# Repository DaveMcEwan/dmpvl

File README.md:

dmpvl - Dave McEwan's Personal Verilog Library
==============================================

Verilog/SystemVerilog projects.

  - doc - External documentation.
  - hdl - HDL (Hardware Description Language) code shared between projects.
  - misc - Miscellaneous items related to this repository.
  - mk - A collection of makefile fragments.
  - prj - A concrete realisation of code on a specific platform.
    May be a specific type of simulation, FPGA, or (wishfully!) ASIC.
    Each of these has some practical usecase.
  - prs - Presentation material like slidesets or papers.
  - tb - Testbenches for verifying modules by simulation.
    These don't really have any practical usecase other than verification.
  - verif - Components which may be shared between verification tasks.

FOSS tools are preferred.

  - iverilog - Traditional event based simulator.
  - verilator - Cycle accurate simulator.
  - yosys - Synthesis.
  - arachne-pnr - First-generation place-and-route for Lattice ice40 FPGAs.
  - nextpnr-ice40 - Second-generation place-and-route for Lattice ice40 FPGAs.
  - tinyprog - Bootloader interface utility for TinyFPGA series of boards.
  - icestorm - Collection of utilities for Lattice ice40 FPGAs.
  - gtkwave - Value Change Dump (VCD) waveform viewer.
    The config file here `.gtkwaverc` may be symlink/copied to `$HOME` or
    appropriate working directories.

Begin work with something like:
```
sudo make -f mk/tools.mk apt_prereqs
make -f tools.mk
export PATH=$PWD/tools/bin:$PATH
```

To track the size of this repo by number of lines of code:

    wc -l `find hdl/ prj/ tb/ verif/ -type f | grep -vP '(build|svg)'`

TODO: More writeup
TODO: Writeup each project.
TODO: Writeup each testbench.

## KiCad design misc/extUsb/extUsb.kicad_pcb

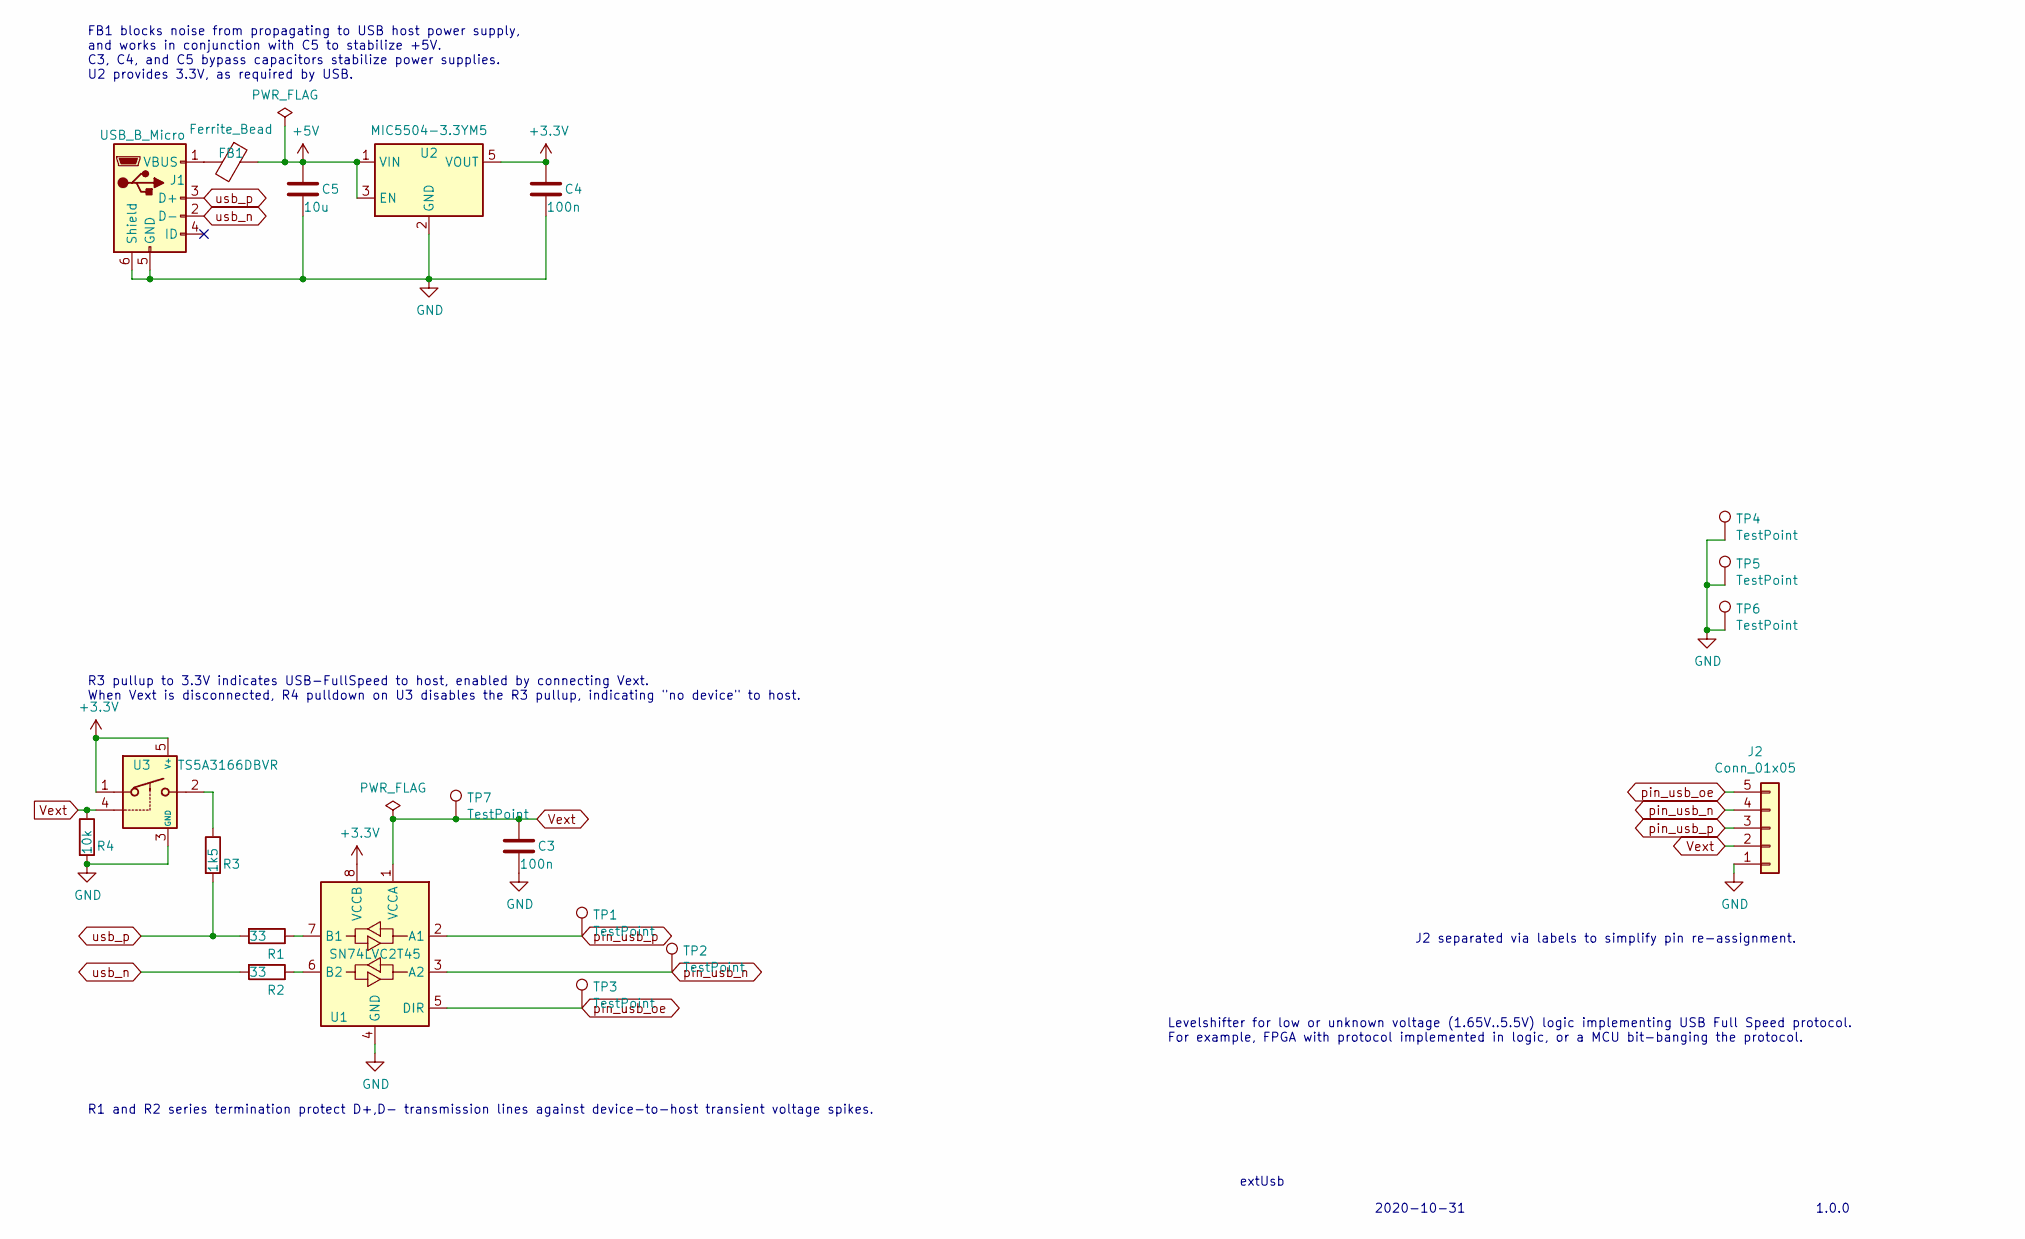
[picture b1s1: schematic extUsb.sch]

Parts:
C3, C4: 100n; C_0603_1608Metric_Pad1.08x0.95mm_HandSolder
C5: 10u; C_0603_1608Metric_Pad1.08x0.95mm_HandSolder
FB1: Ferrite_Bead; L_0603_1608Metric_Pad1.05x0.95mm_HandSolder
J1: USB_B_Micro; USB_Micro-B_Molex-105017-0001
J2: Conn_01x05; PinHeader_1x05_P2.54mm_Horizontal
R1, R2: 33; R_0603_1608Metric_Pad0.98x0.95mm_HandSolder
R3: 1k5; R_0603_1608Metric_Pad0.98x0.95mm_HandSolder
R4: 10k; R_0603_1608Metric_Pad0.98x0.95mm_HandSolder
TP1: TestPoint
TP2, TP3, TP4, TP5, TP6, TP7: TestPoint; TestPoint_Pad_D2.0mm
U1: SN74LVC2T45; SSOP-8_2.95x2.8mm_P0.65mm
U2: MIC5504-3.3YM5; SOT-23-5_HandSoldering
U3: TS5A3166DBVR; SOT-23-5_HandSoldering

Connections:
+3V3: C4.1, U1.8 (VCCB), U2.5 (VOUT), U3.1, U3.5 (V+)
+5V: C5.1, FB1.1, U2.1 (VIN), U2.3 (EN)
GND: C3.2, C4.2, C5.2, J1.5 (GND), J1.6 (Shield), J2.1, R4.2, TP4.1, TP5.1, TP6.1, U1.4 (GND), U2.2 (GND), U3.3 (GND)
unnamed: FB1.2, J1.1 (VBUS)
unnamed: R1.1, U1.7 (B1)
unnamed: R2.1, U1.6 (B2)
unnamed: R3.1, U3.2
Vext: C3.1, J2.2, R4.1, TP7.1, U1.1 (VCCA), U3.4
pin_usb_n: J2.4, TP2.1, U1.3 (A2)
pin_usb_oe: J2.5, TP3.1, U1.5 (DIR)
pin_usb_p: J2.3, TP1.1, U1.2 (A1)
usb_n: J1.2 (D-), R2.2
usb_p: J1.3 (D+), R1.2, R3.2

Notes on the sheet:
R1 and R2 series termination protect D+,D- transmission lines against device-to-host transient voltage spikes.
FB1 blocks noise from propagating to USB host power supply, and works in conjunction with C5 to stabilize +5V. C3, C4, and C5 bypass capacitors stabilize power supplies. U2 provides 3.3V, as required by USB.
J2 separated via labels to simplify pin re-assignment.
Levelshifter for low or unknown voltage (1.65V..5.5V) logic implementing USB Full Speed protocol. For example, FPGA with protocol implemented in logic, or a MCU bit-banging the protocol.
extUsb
2020-10-31
1.0.0
R3 pullup to 3.3V indicates USB-FullSpeed to host, enabled by connecting Vext. When Vext is disconnected, R4 pulldown on U3 disables the R3 pullup, indicating "no device" to host.

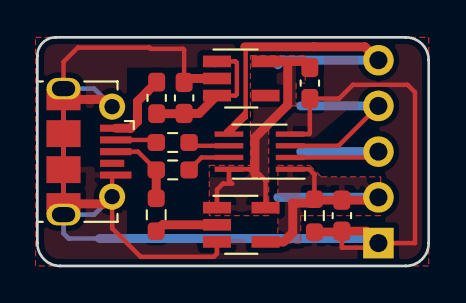
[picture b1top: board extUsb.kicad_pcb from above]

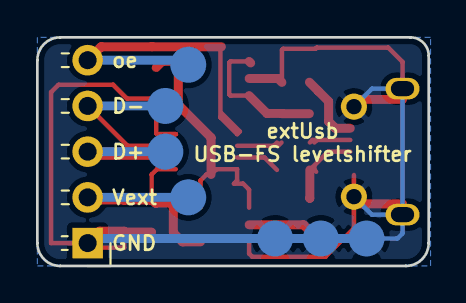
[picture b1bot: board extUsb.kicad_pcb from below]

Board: 2 copper layers, 21.7 x 12.7 mm, 20 parts (8 on the bottom side), 13 nets.

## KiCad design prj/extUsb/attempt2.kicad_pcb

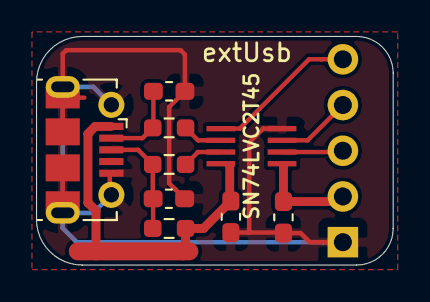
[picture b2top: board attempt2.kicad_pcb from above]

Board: 2 copper layers, 19.8 x 12.7 mm, 10 parts (1 on the bottom side), 10 nets.

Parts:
C1, C2: 18pF; C_0603_1608Metric_Pad1.05x0.95mm_HandSolder
C3, C4: 100nF; C_0603_1608Metric_Pad1.05x0.95mm_HandSolder
J1: USB_B_Micro; USB_Micro-B_Molex-105017-0001
J2: Conn_01x05; PinHeader_1x05_P2.54mm_Horizontal
R1: 1k5; R_0603_1608Metric_Pad0.98x0.95mm_HandSolder
R2, R3: 33; R_0603_1608Metric_Pad0.98x0.95mm_HandSolder
U1: SN74LVC2T45; SSOP-8_2.95x2.8mm_P0.65mm

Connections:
GND: C1.2, C2.2, C3.1, C4.1, J1.5, J1.6, J2.1, U1.4
unnamed: R2.1, U1.7
unnamed: R3.1, U1.6
Vext: C4.2, J2.2, U1.1
Vusb: C3.2, J1.1, R1.1, U1.8
pin_usb_n: J2.4, U1.3
pin_usb_oe: J2.5, U1.5
pin_usb_p: J2.3, U1.2
usb_n: C2.1, J1.2, R3.2
usb_p: C1.1, J1.3, R1.2, R2.2

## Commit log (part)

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2020-05-30 correlator Separate LOGDROP_PRECISION from MAX_WINDOW_LENGTH_EXP.
2020-05-30 logdropWindow Comment corrections.
2020-05-30 correlator sampleRateNegExp
2020-05-31 hdl/strobe
2020-06-01 correlator WIP NONFUNCTIONAL PktFifo flush,depth
2020-06-05 typo
2020-06-08 tb/common.mk V_INCDIRS
2020-06-09 tb/correlator ptyBytePipe DPI object now linking.
2020-06-10 ptyBytePipe Nicer VERB messages.
2020-06-11 tb/correlator WIP NONFUNCTIONAL Starting tbCtrl
2020-06-16 verif/dmpvlCommon.h Take ERROR and VERB from ptyBytePipe
2020-06-16 tb/correlator First signs of life from tbCtrl.
2020-06-17 tb/correlator First hookup to correlator.py NONFUNCTIONAL
2020-06-19 tb/correlator More verbosity to help match up waveform with logfile.
2020-06-19 correlator Whitespace and convenience localparams.
2020-06-19 tb/correlator Start faster and put a few steps at the end of waveform.
2020-06-19 VerilatorCtrlTb Print walltime with each tick.
2020-06-23 tb/correlator Trace down to u_prngJitter.
2020-06-23 correlator,strobe Correct ctrlPeriod/ctrlPeriodM1 behaviour.
2020-06-23 correlator,strobe Jitter functionallity.
    Period is now (almost) equally likely to be longer and shorter than
    exact length specified by samplePeriodExp.
    Actual mean period is (2**samplePeriodExp + 0.5) samples.
2020-06-28 tb/logdrop,strobe Plot,diagram fixes
2020-07-01 correlator_tui Reverse option --no-prog to --prog, add --no-init.
    Allows working between interactive and scripted recording mode (in future).
2020-07-01 correlator_tui sampleJitter unit is cycles not samples.
2020-07-02 correlator bpReg protocol fix for reading pktfifo
2020-07-02 correlator Timeout argument and correct end of tbCtrl sequence.
2020-07-03 correlator,strobe Use i_cg everywhere.
2020-07-03 correlator Parameterize pktfifo DEPTH.
2020-07-03 correlator Both rectangular and logdrop count in fx format.
2020-07-04 correlator Register window counts for transmission.
2020-07-04 correlator Logdrop window counter format/width fix.
2020-07-04 rm corrdet Unused and incomplete block now superseded by correlator.
2020-07-04 correlator LED with PWM control.
2020-07-05 correlator Update info section of TUI.
2020-07-06 correlator Cosmetic tidy/organize.
2020-07-07 tb/dividerFsm Add o_done for easier sample logic.
2020-07-09 dividerFsm comment-only
2020-09-30 Move *.vh to *.svh
2020-09-30 Move *.v to *.sv as everything is coded in SV2005.
    Vivado appears to require this extension for check_syntax to pass.
2020-10-01 Fix warnings from Vivado.
2020-10-01 Move correlation counters to hdl/
2020-10-01 correlator_ZC702 WIP Initial copy from eg-zc702.
2020-10-02 correlator Initial synthesis for VC707
2020-10-04 prngXo(ro)shiro* rm unused i_rst
2020-10-04 correlator_XilinxDev fix direction of GPIO_LED_0
2020-10-04 Vivado check_syntax should find headers.
2020-10-04 correlator_VC707/correlator.sv Reorder file to avoid use-before-defined warnings.
2020-10-06 correlator_VC707 Also lint with yosys.
2020-10-06 rm unused Vivado scripts.
2020-10-06 correlator_VC707 Extra flop stage on prodXY for DSP481E to set MREG=1 and PREG=1.
2020-10-06 correlator_VC707 vivado.tcl getopt
2020-10-08 correlator Plumb extra layer of hierarchy to cleanly split top level and register interface.
2020-10-08 correlator Pass through missed parameters.
2020-10-09 hdl/xbar Initial add.
2020-10-09 correlator Initial support for N_PAIR.
2020-10-09 correlator N_PAIR=2
    Just meets timing but changing PNR_SEED to 1 gives slightly faster.
2020-10-12 correlator Add another layer of hierarchy to avoid repeated plumbing in tb.
2020-10-13 correlator Addr decode bug in bpReg.
2020-10-13 correlator Proper terminology for X/Y mux selects.
2020-10-13 correlator comment-only
2020-10-16 correlator_VC707 Large parameters for N_PROBE,N_ENGINE when building for XM105 daughterboard.
2020-10-20 tools.mk/ngspice
2020-10-22 tb/pwmFilter Basic ngspice transient and AC analysis.
2020-10-26 correlator_VC707 Make signoff default target.
2020-10-26 correlator_Zedboard Initial port using VC707 as base.
    PS7 block is not instanced yet so may everything may fail.
2020-10-28 usbfsSerialEchoer Initial support for extUsb.
    TXB0104 levelshifters are incompatible because the 1.5kOhm pullup on D+ prevents direction sensing.
    Next trying SN74LVC2T45 with direction control and explicit mention of pullups in app note.
2020-10-28 extUsb PNGs for convenience
2020-10-29 extUsb attempt2 Still missing 3.3V regulator.
2020-10-31 mv docs for extUsb to separate subdir
2020-10-31 extUsb Layout for hand-solder
2020-10-31 extUsb rm attempt2
2020-11-01 extUsb release to DirtyPCBs
2020-11-04 extUsb BOM and release to UoB
2020-11-06 correlator Zedboard assign pins for extUsb face down in JA1
2020-11-08 extUsb Analog switch for 1k5 pullup
2020-11-08 extUsb Schematic passing DRC and release for analog switch.
2020-11-09 correlator_Zedboard Update Make/TCL flow for Vivado.
2020-11-09 correlator_Zedboard WIP XM105/extUsb support, building but not tested.
2020-11-10 correlator_Zedboard Minor cleanups noticed in VC707 port.
2020-11-10 corrOPA submodule init
2020-11-12 usbfsSerialEchoer Commented constraints for testing extUsb.
2020-11-13 extUsb Missed new keepouts
2020-11-13 corrOPA patch for system.v
    Also contains a few auto whitespace changes.
2020-11-16 corrOPA Constraints copied for FMC1.
    Implementation currently failing due to something with mmcm.
2020-11-17 corrOPA Route corr_clk out to top level, bitstream generates.
2020-11-18 corrOPA Wait for center pushbutton before booting.
2020-11-19 hdl/pushbutton Initial design for use in corrOPA
2020-11-19 tb/pushbutton With real-world result.
2020-11-19 corrOPA Makefile minor tidy.
2020-11-23 BytePipe Description update.
2020-11-25 corrOPA README
2020-11-26 correlator Separate X and Y jittery strobes from non-jittery antiphase counter strobe.
    TODO: Packet fifo has not been considered here - it is probably broken.
2020-11-27 xbar Correct select (previously untested)
2020-11-27 tb/correlator GtkWave save file
2020-11-27 corrOPA List NoC connections
2020-11-27 tb/correlator Nicer plot and compress to FST.
2020-11-30 hdl/syncBit Replace pushbutton with more general single bit sync module.
2020-12-01 syncBit Correct use of N_SYNC parameter which was confusing.
2020-12-01 fifo Change to valid/ready interface instead of push/pop.
2020-12-01 fifo wrptr->wptr, rdptr->rptr
2020-12-01 pwm comment-only typos
2020-12-01 hdl/cdcFifo WIP
    Still to implement dff stripe for FAST_NOT_SMALL.
    Untested.
2020-12-04 tb/fifoScoreboards WIP Now building but not checking output.
2020-12-04 cdcData Linear accept data on correct cycle.
2020-12-05 tb/fifoScoreboards Delete VCD after conversion to FST, and rm column.
2020-12-06 cdcFifo revert
2020-12-06 Add fifoScoreboards to top level checks.
2020-12-06 cdcFifo Basic structure for fast topology. Slow still passes, fast is WIP.
2020-12-06 cdcFifo Separate read and write domains, slowSmall/fastLarge topology parameter on individual sides.
2020-12-08 corrOPA Makefile fixes, pushbutton->syncBit, fifo->fifoW1R1
2020-12-08 corrOPA Separate resets for OPA and correlator to allow multiple bootruns without reconfiguring.
2020-12-09 corrOPA Archive known working bitstream.
2020-12-14 common_ice40.mk Simplify and unify TinyFPGA-BX projects.
2020-12-24 logdropWindow/plot Notation convention as per Wikipedia.
2020-12-31 tb/logdropWindow Plot improvements for large N, in line with chapter4 of thesis.
2021-01-08 correlator multipnr N_ENGINE=3
2021-03-04 Fix correlator_VC707 in prep for UST.
2021-03-09 Expose full pkt at correlator interface in prep for UST integration.
2021-03-10 Read HDL with more non-FOSS tools.
2021-03-11 WIP Top level for minProtoUst_VC707. UNFINISHED
2021-03-12 minProtoUst Compiling to bitstream.
2021-03-15 minProtoUst Buildable connection-utils.
2021-03-16 minProtoUst Attempting first connection
2021-03-17 minProtoUst First connection made
2021-03-17 minProtoUst General discovery passing.
2021-03-18 First steps of consistent Makefile fragments.
2021-03-19 prj/correlator All rules working.
2021-03-19 prj/usbFullSpeedSerial
2021-03-19 prj/usbfsXoroshiro
2021-03-19 prj/correlator_Zedboard
2021-03-19 tools
2021-03-19 tb/fxcs
2021-03-21 Ignore specific test bitfile.
2021-03-23 minProtoUst,corrOPA First test returning data at regular intervals.
2021-03-24 csv.mk for fifoScoreboards
2021-03-25 corrOPA probe mapping
2021-03-25 tb/bpRegMem
2021-03-29 corrOPA dummyload for multi-process system.
2021-03-30 corrOPA Archive bitstream used for gathering datasets.
2021-04-06 doc BLIF
2021-04-06 multipnr VGW_usbserial
2021-04-29 mssbIdx comment-only
2021-05-25 mv probsys0 -> praxi
    Consistent naming with thesis.
2021-06-01 mv prj/praxi tb/praxi
2021-06-01 Don't lint TBs with yosys
2021-06-01 tb/onehotIdx
2021-06-01 tb/pushbutton
2021-06-01 tb/usbFullSpeedPackets
2021-06-01 tb/usbFullSpeedTransactions
2021-06-01 tb/usbfsBpRegMem
2021-06-01 tb/fifoW1R1
2021-06-01 tb/correlator
2021-06-30 mssbIdx Comment typo.
2021-07-20 doc/Anger_Optimization_Manuals
2021-08-09 doc 7-Series overview
2021-10-01 tb/foo
2021-10-01 prs Foo
2021-10-01 BoringFlops Begin tool support section.
2021-11-05 Initial support for svlint.
2021-12-29 prs hierColor
2022-01-21 prs SystemVerilog examples of undesirable practice.
2022-02-01 ifdefFragments Examples for pp-free parser in prep for svfmt.
2022-02-04 prs/logic_symbols Add comparators and muxes.
2022-02-18 doc IEEE1800-2017
2022-03-09 style_commaleading Tidy, corrections, add module instances.
2022-04-21 doc/UPF 1801
2022-05-19 doc/ieee1364-2001
2022-05-25 style_commaleadyng Increase indent.
2022-06-21 prs/style_paramcheck.sv Examples of parameter constraint checks.
2022-07-15 hierColor prefix/arrow vs noPrefix/noArrow
2022-08-18 prs/ParameterDatatypes WIP/UNFINISHED
2022-08-18 prs/doc/booktabs
2022-08-19 prs/ParameterDatatypes Test inline LaTeX, again.
2022-08-23 prs/ParameterDatatypes Finished main body of paper, begin example SV.
2022-08-24 prs/ParameterDatatypes Correct/clarify EB_VEC1D.
2022-08-25 prs/ParameterDatatypes Tidy makefile
2022-08-25 prs/ParameterDatatypes Attempt to tidy both PDF and in-browser rendering.
2022-08-26 prs/ParameterDatatypes Updates after first round of feedback.
    - Separate section on default assignments.
    - New section on v95 parameter checks.
    - Minor fixes.
2022-08-26 style_paramcheck Add v95-compatible style.
2022-08-29 prs/ParameterDatatypes Add (placeholder) support for VCS.
2022-08-29 prs/ParameterDatatypes Add support for verilator.
2022-09-03 doc/SpaceWire
2022-10-12 paper/ChecklistForEngineeringChanges Initial idea.
2022-10-17 paper/ChecklistForEngineeringChanges Pre-build PDF.
2022-10-20 paper/ChecklistForEngineeringChanges chmod -x
2022-10-20 paper/ChecklistForEngineeringChanges Remove page numbers.
2022-10-27 prs/PropertiesBeyondAssertions More placeholder text.
2022-11-01 prs/ChecklistForEngineeringChanges Reword epilogue in condensed version.
2022-12-06 paper/AISH PropertiesBeyondAssertions -> AssertionsInPhysicalHardware
2023-01-09 AISH Continue explanation of method.
2023-01-11 prs/BoringFlops Usecases for consistent style.
2023-12-17 prs/shr/sv
2023-12-17 doc IEEE specs I'm using most days
2023-12-17 prs Introduction to Version Control and Git
